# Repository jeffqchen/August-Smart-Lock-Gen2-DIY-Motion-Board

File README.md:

# August Smart Lock Gen2 DIY Motion Board

The 2nd Generation August Smart Lock has a design flaw - its motion sensing board has a fused ribbon cable design that conveniently connects to the main board.

With the lock rotating back and forth over the years, the joint where the ribbon cable meets the rigid PCB backing is fatigued and will eventually snap. This will mark the end of the part, and as well as the lock itself.

The lock will be unable to tell its current position. When powered on, the LED will flash red. The lock will be able to unlock but unable to lock again, end up in a stuck state, complaining that something went wrong. Attempting to recalibrate the lock will fail as well.

With this DIY PCB, you will be able to transfer the chip from the broken board, and connect the board to the main board with a socketed ribbon cable connector. Even if the ribbon cable breaks again in the future, you will just have to swap in another ribbon cable, which is much easier.

---------
## Parts

-  [PCB](https://oshpark.com/shared_projects/Z0Jr2p2V) (remember to order with 0.8mm thickness)

### Passive parts

You can transfer these from the old board, or use SMD 0603 size ones instead.

- 0 Ohm Resistor
- 10K Ohm Resistor
- 100nF Capacitor

### Chip

The main chip on the board, looks like to be MEMS accelerometer from STM, probably a LIS3DHTR. I suggest you transfer this chip from the old board to the new one for the best result.

### Ribbon Cable & Connector

I used a 6 position FPC cable and corresponding socket to connect to the main board.

- 6 Position 0.5mm Pitch FPC & Connector - [Link](https://github.com/jeffqchen/JeffParts/blob/main/Connectors/6%20Position%200.5mm%20Pitch%20FPC%20%26%20Connector/info.md)

You may also choose to use the 100mm version of the flex cable if 50mm is too short for you. You will have to make a loop to route the extra length inside the shell, but it's better than ripping the connector off of the PCB.

---------
## Assembly

The knowledge on how to use a hot air rework station is required for this DIY board.

For the accelerometer chip, all pads on both the chip and the PCB have to be well-tinned. Heat the chip from either top or bottom of the PCB in order to melt it onto the PCB.

For the connector, use proper amount of tin or solder paste on the pads, place the connector, and then apply hot air from THE BOTTOM of the PCB in order to solder the connector into place. Note the black locking tab is on the back of the connector, not the front, unlike what you usually see.

For the rest of the passive components, you can either put in replacement 0603 ones, or transfer the original ones from the official PCB - although this is more challenging due to their tiny size.

And finally, plug in the FPC with contacts facing up into the connector, then close the tab on the back of the connector

---------
## Installation

How the original came out, you put the replacement right back in the same way.

If this is your first time taking apart the lock, you must pay attention to the orientations of the outer ring and the center gear/PCB assembly. Otherwise the lock will end up in a weird position, making using it very awkward, or even snapping/breaking the new flex cable or PCB you just put in when you attempt to turn the lock.

Using the 100mm flex cable and carefully routing the extra length inside the lock seem to fare better than just using the 50mm cable, which felt slightly too short and introduced too much tension on the two ends of the flex cable.

---------
## Notes

After installing this PCB, the connector fell off the board after a few days of use, and had to be re-soldered. This is why I suggest trying the 100mm FPC instead of the 50mm one. You might also want to strengthen the connector with super glue or a section of metal wire. But after all, it's better than something that breaks and become unfixable.

---------
Shield: [![CC BY-SA 4.0][cc-by-sa-shield]][cc-by-sa]

This work is licensed under a
[Creative Commons Attribution-ShareAlike 4.0 International License][cc-by-sa].

[![CC BY-SA 4.0][cc-by-sa-image]][cc-by-sa]

[cc-by-sa]: http://creativecommons.org/licenses/by-sa/4.0/
[cc-by-sa-image]: https://licensebuttons.net/l/by-sa/4.0/88x31.png
[cc-by-sa-shield]: https://img.shields.io/badge/License-CC%20BY--SA%204.0-lightgrey.svg

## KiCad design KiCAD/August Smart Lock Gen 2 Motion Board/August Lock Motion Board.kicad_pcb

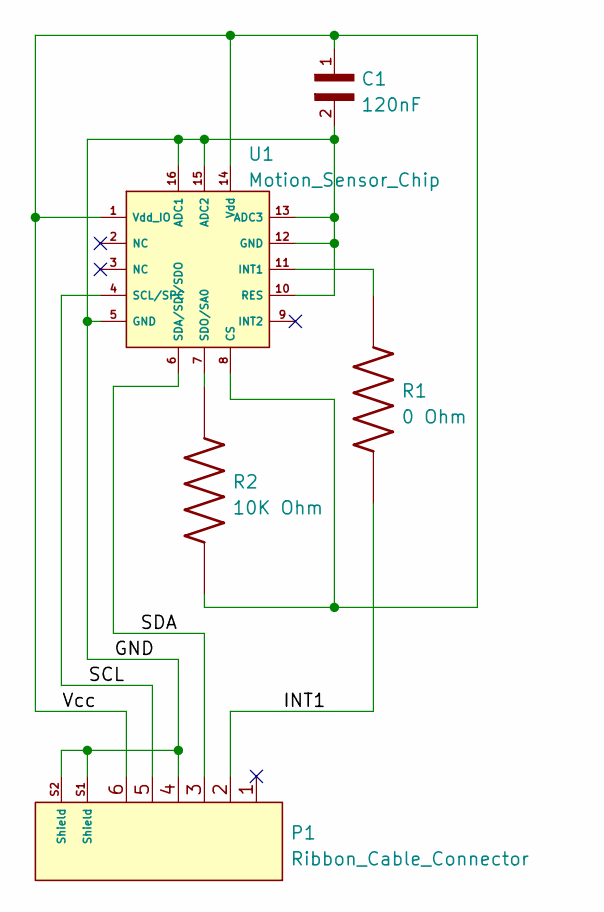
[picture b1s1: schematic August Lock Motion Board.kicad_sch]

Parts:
C1: 120nF; C_0603_1608Metric
P1: Ribbon_Cable_Connector; Ribbon Connector
R1: 0 Ohm; R_0603_1608Metric
R2: 10K Ohm; R_0603_1608Metric
U1: Motion_Sensor_Chip; Motion_Chip

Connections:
/GND: C1.2, P1.4, P1.S1 (Shield), P1.S2 (Shield), U1.5 (GND), U1.10 (RES), U1.12 (GND), U1.13 (ADC3), U1.15 (ADC2), U1.16 (ADC1)
/INT1: P1.2, R1.1
/SCL: P1.5, U1.4 (SCL/SPC)
/SDA: P1.3, U1.6 (SDA/SDI/SDO)
/Vcc: C1.1, P1.6, R2.2, U1.1 (Vdd_IO), U1.8 (CS), U1.14 (Vdd)
unnamed: R1.2, U1.11 (INT1)
unnamed: R2.1, U1.7 (SDO/SA0)

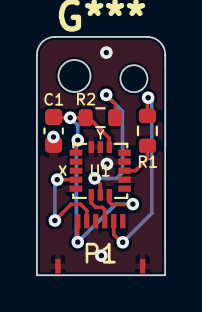
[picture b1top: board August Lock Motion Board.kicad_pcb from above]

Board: 2 copper layers, 7.1 x 13.2 mm, 5 parts (0 on the bottom side), 7 nets.

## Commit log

2022-08-12 Add KiCAD files
2022-08-16 Readme write up
